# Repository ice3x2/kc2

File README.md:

# kc2

- **[최신 PCB · 주문한 거버 · 인쇄 모델 — hardware](hardware/README.md)**
- [PCB 프로젝트](hardware/PCB/) · [주문한 거버 ZIP](hardware/GERBER/) · [하우징·링 모델](hardware/MODELS/)
- [MX · Choc V1 · Deep Sea 내부 충전형 인쇄 안내](hardware/MODELS/PRINT-filled-plates.md) · [검증 기록](docs/reports/solid-filled-plates-20260913/README.md)
- [자석 홈 옵션 / 무자석 옵션 선택 안내](hardware/MODELS/PRINT_magnetic.md)
- [주문 당시 안내 원본](order.md) — 봉인 해시 보존용입니다. 현재 위치는 위 `hardware` 안내를 보세요.
- [요구사항 원본(SRS)](docs/spec/00.index.md)

새로 clone한 뒤 기존 생성·검증 도구를 사용할 때는 한 번 실행하세요(Python 3.12 이상).

```powershell
python -B -m tools.kc2_current_layout --apply
```

현재 파일은 `hardware/PCB`, `hardware/GERBER`, `hardware/MODELS`에 실제로 저장됩니다. 기존 `hardware/case`와 일부 `hardware/kicad` 경로는 동일 원본을 가리키는 로컬 호환 연결이며 복사본이 아닙니다.

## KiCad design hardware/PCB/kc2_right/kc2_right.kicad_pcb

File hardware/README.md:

# PCB · 주문한 거버 · 하우징 인쇄 파일

요구사항: `CON-ARCH-006`, `CON-ARCH-007`, `OPS-ARCH-006/007`.

하우징을 인쇄하기 전에 [현재 인쇄·조립 안내](MODELS/PRINT-upper-finish.md)의 검증 명령을 실행하세요. 상판의 비기능 내부 틈을 메우고 국부 하향 돌출을 제거하여 아홉 상판 STL의 최저면을 `Z=4.40`으로 공면화한 개정입니다. 검증이 실패하거나 manifest가 없으면 게시가 미완료된 것이므로 인쇄를 보류합니다. 실제 끼움·강도·키캡 간섭·나사 토크는 출력·조립 후 확인해야 합니다.

- `PCB/`: 기존 주문 설계. [왼쪽 PCB](PCB/kc2_left/kc2_left.kicad_pcb), [오른쪽 PCB](PCB/kc2_right/kc2_right.kicad_pcb). 각 KiCad 프로젝트 폴더 전체와 저장소 `third_party` 라이브러리를 유지하세요.
- `GERBER/`: 변경하지 않은 주문 r4 PCB-only 패키지. [왼쪽 제조 ZIP](GERBER/kc2_left-pcb-fabrication-only.zip), [오른쪽 제조 ZIP](GERBER/kc2_right-pcb-fabrication-only.zip), [주문 manifest](GERBER/manifest.json). 이번 기구 개정으로 재주문할 필요는 없습니다.
- `MODELS/`: MX / Choc V1 / Deep Sea Mini 상판과 무자석 / magnetic 하판. 각 종류의 왼쪽 한 개와 오른쪽 A/B 두 STL을 사용합니다. 오른쪽 STEP/F3D는 두 부품을 포함하는 편집·확인용입니다.
- `MODELS/adapters/`: 이번에 변경하지 않은 [기존 링 어댑터](MODELS/adapters/README.md).

PCB는 이전처럼 하판 받침 위에 놓습니다. 외벽은 PCB 윗면보다 1.50 mm 높고 상판 아래쪽을 1.20 mm 감쌉니다. 중앙 좌우 맞댐은 비접촉이며 잠금 요철은 없습니다. 오른쪽 A/B 결합부는 별도 구조입니다. 이전 상판·하판과 새 파일을 섞지 말고 현재 안내의 정확한 15개 STL 링크 중 필요한 종류를 선택하세요.

실리콘 발 배치·접착 검토는 사용자 요청으로 보류했습니다. 예전 발 배치 그림은 이번 하우징의 검증 증거가 아닙니다. 기존 `PRINT-filled-plates.md` 등 과거 안내는 현재 게시 검증을 대체하지 않습니다. 현재 인쇄 안내가 이전 지침보다 우선합니다.

이 기구 개정은 이미 주문한 PCB/Gerber 16개 파일을 변경하지 않으며 새로운 제작·구매·결제 승인을 의미하지 않습니다.

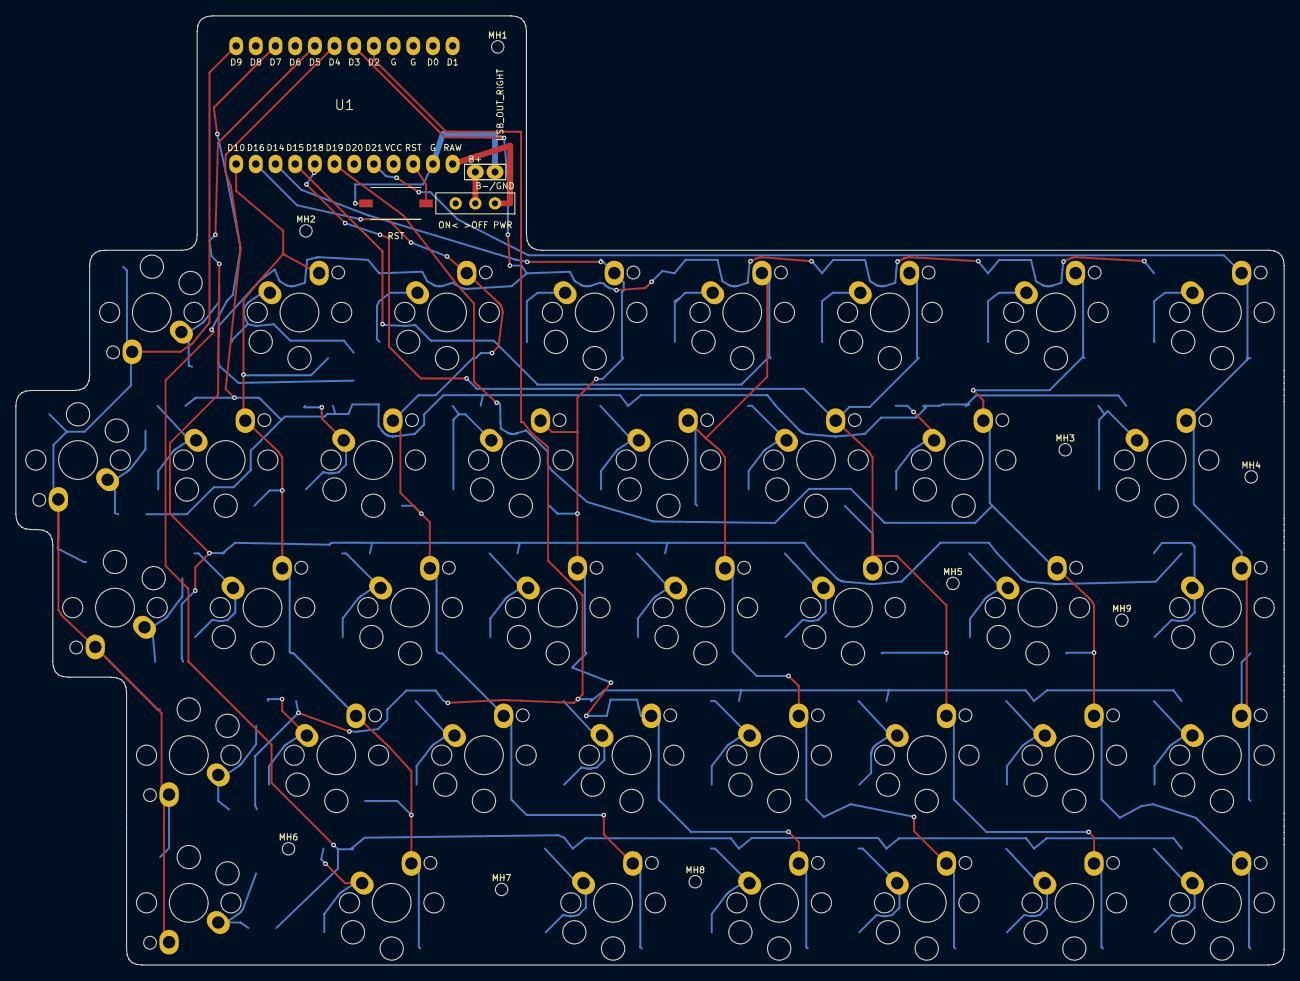
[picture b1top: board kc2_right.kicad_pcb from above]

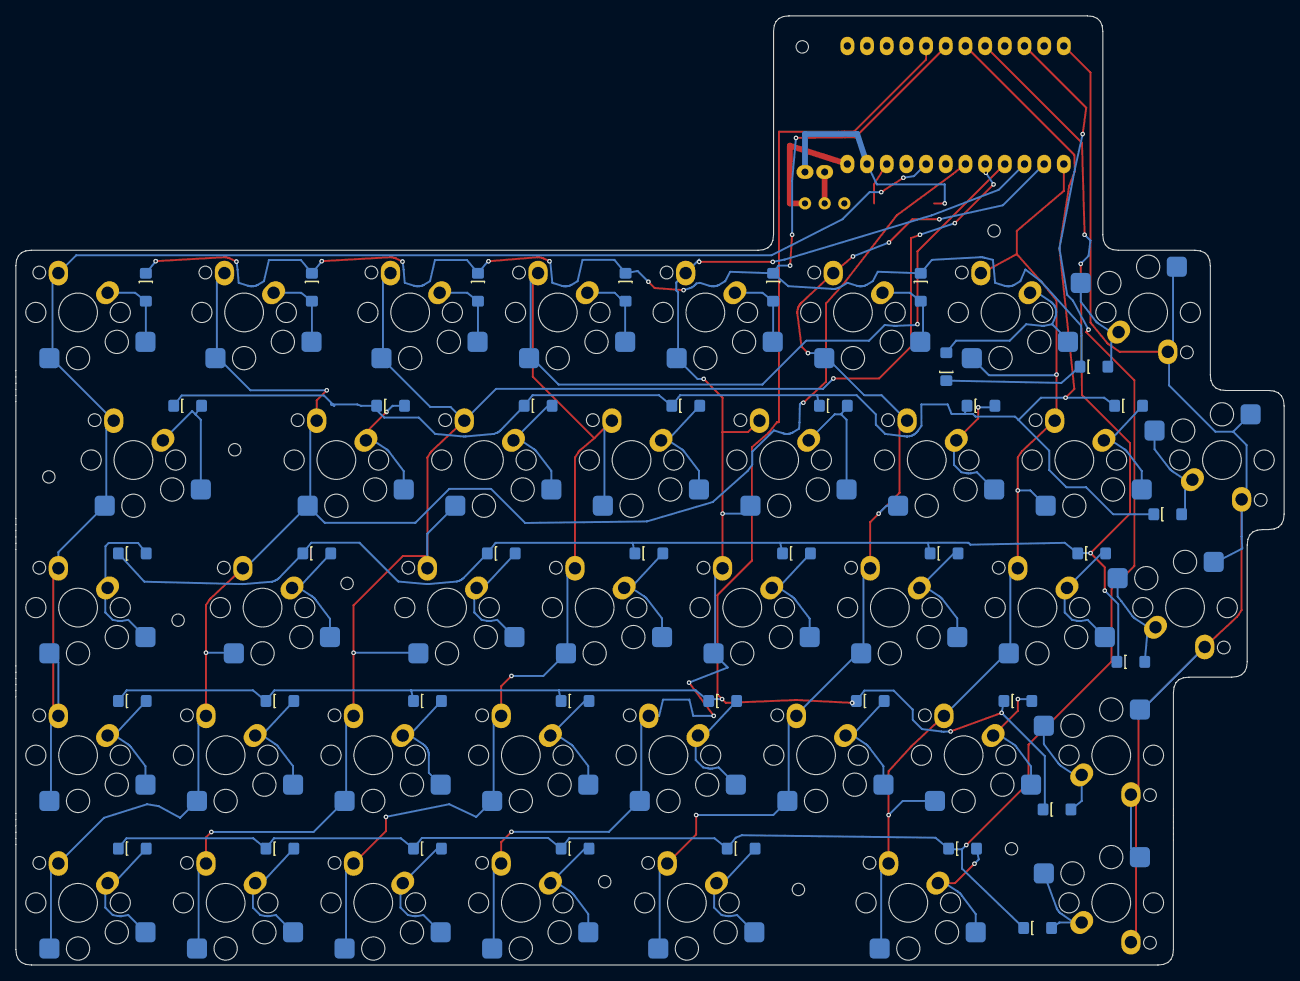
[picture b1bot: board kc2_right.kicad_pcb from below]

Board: 2 copper layers, 163.7 x 122.5 mm, 93 parts (39 on the bottom side), 56 nets.

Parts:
BAT1: 301230_3.7V_100mAh; BAT_301230_30x12mm
BAT_LEAD_SLOT1: BAT_LEAD_NPTH_SLOT_3.6x2.2
D1, D2, D3, D4, D5, D6, D7, D8, D9, D10, D11, D12, D13, D14, D15, D16, D17, D18, D19, D20, D21, D22, D23, D24, D25, D26, D27, D28, D29, D30, D31, D32, D33, D34, D35, D36, D37, D38, D39: 1N4148W-13-F_DiodesInc_SOD123; D_1N4148W_SOD123_HandSolder_DiodesInc
J_BAT1: 301230_DIRECT_SOLDER; BAT_2Pin_PTH_DirectSolder
MH1, MH2, MH3, MH4, MH5, MH6, MH7, MH8, MH9: M1.4_NPTH_1.60; MH_M1.4_NPTH_1.60
SW1: KEY_01; SW_Choc_V2_Socket_MX_THT
SW2: KEY_02; SW_Choc_V2_Socket_MX_THT
SW3: KEY_03; SW_Choc_V2_Socket_MX_THT
SW4: KEY_04; SW_Choc_V2_Socket_MX_THT
SW5: KEY_05; SW_Choc_V2_Socket_MX_THT
SW6: KEY_06; SW_Choc_V2_Socket_MX_THT
SW7: KEY_07; SW_Choc_V2_Socket_MX_THT
SW8: KEY_08; SW_Choc_V2_Socket_MX_THT
SW9: KEY_09; SW_Choc_V2_Socket_MX_THT
SW10: KEY_10; SW_Choc_V2_Socket_MX_THT
SW11: KEY_11; SW_Choc_V2_Socket_MX_THT
SW12: KEY_12; SW_Choc_V2_Socket_MX_THT
SW13: KEY_13; SW_Choc_V2_Socket_MX_THT
SW14: KEY_14; SW_Choc_V2_Socket_MX_THT
SW15: KEY_15; SW_Choc_V2_Socket_MX_THT
SW16: KEY_16; SW_Choc_V2_Socket_MX_THT
SW17: KEY_17; SW_Choc_V2_Socket_MX_THT
SW18: KEY_18; SW_Choc_V2_Socket_MX_THT
SW19: KEY_19; SW_Choc_V2_Socket_MX_THT
SW20: KEY_20; SW_Choc_V2_Socket_MX_THT
SW21: KEY_21; SW_Choc_V2_Socket_MX_THT
SW22: KEY_22; SW_Choc_V2_Socket_MX_THT
SW23: KEY_23; SW_Choc_V2_Socket_MX_THT
SW24: KEY_24; SW_Choc_V2_Socket_MX_THT
SW25: KEY_25; SW_Choc_V2_Socket_MX_THT
SW26: KEY_26; SW_Choc_V2_Socket_MX_THT
SW27: KEY_27; SW_Choc_V2_Socket_MX_THT
SW28: KEY_28; SW_Choc_V2_Socket_MX_THT
SW29: KEY_29; SW_Choc_V2_Socket_MX_THT
SW30: KEY_30; SW_Choc_V2_Socket_MX_THT
SW31: KEY_31; SW_Choc_V2_Socket_MX_THT
SW32: KEY_32; SW_Choc_V2_Socket_MX_THT
SW33: KEY_33; SW_Choc_V2_Socket_MX_THT
SW34: KEY_34; SW_Choc_V2_Socket_MX_THT
SW35: KEY_35; SW_Choc_V2_Socket_MX_THT
SW36: KEY_36; SW_Choc_V2_Socket_MX_THT
SW37: KEY_37; SW_Choc_V2_Socket_MX_THT
SW38: KEY_38; SW_Choc_V2_Socket_MX_THT
SW39: KEY_39; SW_Choc_V2_Socket_MX_THT
SW_PWR1: IMMS-12V_BSI-10; SW_IMMS_12V_BSI10_THT
SW_RST1: NW3-A06-B3 RST; SW_NW3_A06_B3_SMD
U1: nice!nano_v2_socket_24pin; NiceNanoV2_Socket_24Pin_USB_OUT_RIGHT

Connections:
BAT+: J_BAT1.1, SW_PWR1.1
GND: J_BAT1.2, SW_RST1.2, U1.GND_C
NN_B+: SW_PWR1.2, U1.RAW
RK01_D: D1.2, SW1.2
RK02_D: D2.2, SW2.2
RK03_D: D3.2, SW3.2
RK04_D: D4.2, SW4.2
RK05_D: D5.2, SW5.2
RK06_D: D6.2, SW6.2
RK07_D: D7.2, SW7.2
RK08_D: D8.2, SW8.2
RK09_D: D9.2, SW9.2
RK10_D: D10.2, SW10.2
RK11_D: D11.2, SW11.2
RK12_D: D12.2, SW12.2
RK13_D: D13.2, SW13.2
RK14_D: D14.2, SW14.2
RK15_D: D15.2, SW15.2
RK16_D: D16.2, SW16.2
RK17_D: D17.2, SW17.2
RK18_D: D18.2, SW18.2
RK19_D: D19.2, SW19.2
RK20_D: D20.2, SW20.2
RK21_D: D21.2, SW21.2
RK22_D: D22.2, SW22.2
RK23_D: D23.2, SW23.2
RK24_D: D24.2, SW24.2
RK25_D: D25.2, SW25.2
RK26_D: D26.2, SW26.2
RK27_D: D27.2, SW27.2
RK28_D: D28.2, SW28.2
RK29_D: D29.2, SW29.2
RK30_D: D30.2, SW30.2
RK31_D: D31.2, SW31.2
RK32_D: D32.2, SW32.2
RK33_D: D33.2, SW33.2
RK34_D: D34.2, SW34.2
RK35_D: D35.2, SW35.2
RK36_D: D36.2, SW36.2
RK37_D: D37.2, SW37.2
RK38_D: D38.2, SW38.2
RK39_D: D39.2, SW39.2
RST: SW_RST1.1, U1.RST
R_COL0: SW1.1, SW9.1, SW17.1, SW25.1, SW33.1, U1.D9
R_COL1: SW2.1, SW10.1, SW18.1, SW26.1, SW34.1, U1.D10
R_COL2: SW3.1, SW11.1, SW19.1, SW27.1, SW35.1, U1.D16
R_COL3: SW4.1, SW12.1, SW20.1, SW28.1, SW36.1, U1.D14
R_COL4: SW5.1, SW13.1, SW21.1, SW29.1, SW37.1, U1.D15
R_COL5: SW6.1, SW14.1, SW22.1, SW30.1, SW38.1, U1.D18
R_COL6: SW7.1, SW15.1, SW23.1, SW31.1, SW39.1, U1.D19
R_COL7: SW8.1, SW16.1, SW24.1, SW32.1, U1.D21
R_ROW0: D1.1, D2.1, D3.1, D4.1, D5.1, D6.1, D7.1, D8.1, U1.D3
R_ROW1: D9.1, D10.1, D11.1, D12.1, D13.1, D14.1, D15.1, D16.1, U1.D4
R_ROW2: D17.1, D18.1, D19.1, D20.1, D21.1, D22.1, D23.1, D24.1, U1.D5
R_ROW3: D25.1, D26.1, D27.1, D28.1, D29.1, D30.1, D31.1, D32.1, U1.D2
R_ROW4: D33.1, D34.1, D35.1, D36.1, D37.1, D38.1, D39.1, U1.D7

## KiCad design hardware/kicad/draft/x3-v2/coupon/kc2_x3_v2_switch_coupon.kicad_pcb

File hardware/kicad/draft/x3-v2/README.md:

# KC2 X3 V2 routed draft

Requirements: `CON-ARCH-004`, `CON-ARCH-006`, `CON-ARCH-007`, `REL-ARCH-001`

Status: **DIGITAL PASS - ORDER READY: NO**. Exact V2 service geometry and nets
and fresh KiCad 10.0.3 DRC pass digitally. Ordering remains blocked by exact
301230 pack/protection/lead and `J_BAT1` drill selection, controller-stack fit,
solder/strain-relief/service tests, IMMS power-transition and BLE tests,
populated coupon/first articles, and housing/fastener/2.0 N deflection tests.

These V2 files live only under `hardware/kicad/draft/x3-v2/`. The promoted
`hardware/kicad/kc2_left/` and `hardware/kicad/kc2_right/` projects are the
older verified X3 variant and are not V2 implementation evidence.

## Assembly modes

The two switch modes are mutually exclusive at every key position:

- Choc V2 / PG1353-class: install a Kailh `CPG135001S30`-class hot-swap socket
  on the PCB bottom. Do not directly solder the switch.
- Cherry MX-style 5-pin PCB-mount: install the switch from the PCB top and
  directly solder its two electrical pins. No MX hot-swap socket is supported.
- Choc V1 / PG1350, Choc V2 direct-solder, and MX hot-swap are unsupported.
- Never install both a Choc socket and an MX switch at one key position.

The intended switch remains the Kailh Deep Sea low-profile / PG1353 family,
but its exact manufacturer MPN and controlled drawing revision are still
pending. `Deep Sea`, `Deep Sea Whale`, a reseller nickname, or a family name
is not an orderable part identity. Do not order the switch until those two
fields are bound to the purchased part and its controlled drawing.

The owned hybrid footprint includes an explicit bottom courtyard from
`(-10.25,1.20)` to `(5.25,8.50)` mm. It encloses the complete bottom socket
body and both B.Cu lands with a `0.25 mm` manufacturing allowance.

The left and right boards use their physical split-keyboard orientations. The
bottom-side socket pattern must be read from the PCB bottom; the 1:1 bottom PDF
is already mirrored for a physical bottom view.

## Matrix diode and polarity

The active V2 BOM contains exactly 70 Diodes Incorporated `1N4148W-13-F`
matrix diodes in flat SOD-123 packages, controlled by `DS30086 Rev. 31-2`.
All are assembled on `B.Cu`. Pin/pad 1 is the cathode connected to the row net; pin/pad
2 is the anode connected to the per-key switch net. A physical bottom view is
mirrored relative to KiCad's top/front view, so place the cathode band toward
the marked pad 1 rather than relying on an assumed left/right direction.

The firmware contract remains `col2row`, active-high columns, and active-high
row inputs with pull-downs. The existing pinned build remains zero-wait: no
extra delay before reading inputs and no delay between driven columns. Do not
change those scan delays until a populated physical coupon has passed both
3.0 V and 3.3 V maximum same-row and maximum same-column stress tests. Those
tests remain pending, so these digitally verified boards are not orderable.

## Joined spacing

The joined reference places the right half `0.80 mm` farther outward than the
ordinary `19.05 mm` one-unit transform. Corresponding Choc V2 and MX assembly
modes are evaluated with the same selected cap envelope for each physical key.
All five actual seam pairs have a nominal `1.80 mm` cap-to-cap gap and a
`3.80 mm` row-center PCB gap:

| Row | Pair | Cap widths (left/right) | Center pitch | Center-to-PCB-edge (left/right) |
|---:|---|---:|---:|---:|
| 0 | `6`-`7` | `18.05 / 18.05 mm` | `19.85 mm` | `8.025 / 8.025 mm` |
| 1 | `T`-`Y` | `18.05 / 18.05 mm` | `19.85 mm` | `8.025 / 8.025 mm` |
| 2 | `G`-`H` | `18.05 / 18.05 mm` | `19.85 mm` | `8.025 / 8.025 mm` |
| 3 | `B`-`N` | `18.05 / 18.05 mm` | `19.85 mm` | `8.025 / 8.025 mm` |
| 4 | `Space`-`B` | `32.3375 / 18.05 mm` | `26.99375 mm` nominal (`26.9937 mm` in the routed coordinate serialization) | `15.16875 / 8.025 mm` nominal |

The two complete closed Edge.Cuts outlines are compared segment by segment,
including horizontal stair transitions. Their exact minimum is `1.10 mm`,
created by a direction-aware `0.55 mm` transition stagger. PCBWay's published
`+/-0.20 mm` CNC outline tolerance gives a conservative two-edge lower bound
of `0.70 mm` at that limiting transition. This is digital nominal geometry;
actual half-to-half housing registration and assembled cap/switch play still
require a printed first article.

After soldering an MX switch, trim both electrical terminals after inspection.
The 2.50 mm lower plate has exterior-bottom-open cutouts through the full plate
height for every MX terminal and solder joint, rather than a closed component
cavity. The lateral solder-fillet model includes a 0.30 mm allowance.

The Choc socket and 1N4148W SOD-123 solder-fillet models each include a 0.30 mm
lateral allowance. The routed boards pass the current digital diode gates:
the minima across both halves are 1.946 mm to unused switch NPTH, 1.125 mm to
switch pads and unrelated exposed copper, 2.225 mm to socket bodies, 0.525 mm
between diode and switch-assembly fillet envelopes, and 1.975 mm from the
diode fillet envelope to Edge.Cuts. The diode-to-unrelated-route minima are
0.737 mm left and 0.545 mm right, both above the 0.10 mm gate. Every diode
pad has an unobstructed cardinal solder-tool approach. The enlarged KC2 hand-
solder land is deliberately not the manufacturer's recommended land: implemented
pads are 1.40 x 1.55 mm at 3.60 mm centers, while the official suggested pads
are 0.90 x 0.95 mm at 4.05 mm centers. Regenerated housing evidence provides
0.35 mm cutout XY clearance, 1.525 mm minimum diode perimeter land, and 1.85 mm
nominal / 1.55 mm post-tolerance diode-to-desk clearance. The Choc socket is the
overall open-component limiter at 1.10 mm nominal / 0.80 mm post-tolerance.
This remains digital
evidence only; physical retention, deflection, and populated-coupon tests are
still required before ordering.

## M1.4 retention prototype

The PCB contains eight left and nine right `MH*` features using the owned
`MH_M1.4_NPTH_1.60` footprint. Each is an unnetted, copper-free `1.60 mm`
round NPTH. Each hole is visibly numbered `MH1..MH8` on the left and
`MH1..MH9` on the right using `0.80 mm` / `0.15 mm` front-silkscreen text.
Service is modeled with keycaps removed and either supported switch
type still installed. A final `3.00 mm` vertical PH0 driver envelope and a
provisional non-countersunk rounded pan/button head envelope of maximum
`3.00 x 1.20 mm` clear the modeled Choc V2 and MX assemblies with a separate
`0.25 mm` XY reserve. The driver envelope already includes its search reserve
and must not be buffered a second time.

The matching lower housing provides a `3.00 mm` zero-gap support land and desk
column at every hole, with a provisional `1.10 x 2.80 mm` blind pilot and a
`0.70 mm` closed bottom at the common Z=-1.00 mm desk datum. A separate exact
one-to-one network of 31-left/39-right `2.40 mm` key-load feet provides every
switch center with a local desk load path whose worst center-to-support-edge
distance is `4.3902 mm`, within the `4.40 mm` SOD-123/P3 bound; mounting columns are not credited as typing-load
supports. The provisional 4.00 mm under-head screw
length, exact screw and driver, full-pattern registration, installation and
stripping torque, ten service cycles, keycap-skirt clearance, and 2.0 N
deflection must be proven on physical coupons. These digital files are not a
fastener purchase recommendation and remain not orderable.

## Battery service path

Each half uses one nominal `30.00 x 12.00 x 3.00 mm`, 3.7 V, 100 mAh
301230-class pack above the carrier PCB and below the socketed nice!nano. The
battery centers are left `(131.7125, 50.7500)` and right
`(78.4000, 50.7500)` mm, with the 30 mm axis parallel to the U1 socket rows.
The exact manufacturer/MPN, single-cell protection status, maximum swollen
thickness, lead-exit drawing, and pull limit remain procurement gates.

Only the pack's pre-attached insulated leads are soldered to `J_BAT1`; do not
solder a bare pouch tab and do not add an A2501, JST, or other detachable
battery connector. `J_BAT1` is left `(115.8125, 59.4000)` R180 and right
`(94.3000, 59.4000)` R0. Its visible assembly marks identify pad 1 `B+` and
pad 2 `B-/GND`; the electrical pad nets remain `BAT+` and `GND`, respectively.
The [official nice!nano documentation](https://nicekeyboards.com/docs/nice-nano/)
identifies the carrier's `RAW` and `GND` pins as the battery-positive and
battery-negative connections, so no extra net tie is required.
`BAT_LEAD_SLOT1` remains an unnetted, copper-free
strain-relief feature identified by the exact board text
`BAT STRAIN RELIEF`, at left `(117.9125, 50.7500)` and right
`(92.2000, 50.7500)` mm; it is not a lower battery exit.

The electrical path is
`J_BAT1 BAT+ -> SW_PWR1 pad 1 common -> pad 2 ON -> NN_B+ -> U1 RAW`. Pad 3 is
NC. J_BAT1 B-/GND remains directly connected to
local GND and U1 GND. Keep BAT+ and its GND return paired in the USB-side
corridor and outside the antenna keepout. The lower housing has no TW301525 or
301230 battery-body cavity; it provides only the required U1, J_BAT1,
strain-relief, IMMS lead, and solder-fillet openings.

## Compact controller tab

The V2-only compact-controller layout keeps all 70 key centers and all 17
numbered mounting-hole centers fixed. U1 centers are left
`(132.7125, 50.7500)` and right `(77.4000, 50.7500)` mm. The top Edge.Cuts
centerline is `Y=39.2500 mm`, and the nominal board height is `122.50 mm`.

POWER and RESET occupy the controller-key gap. `SW_PWR1` is left
`(115.8125, 63.4500)` R0 and right `(94.3000, 63.4500)` R180. `SW_RST1` is
left `(126.0625, 63.4500)` R0 and right `(84.0500, 63.4500)` R180, with pad
1=RST on the POWER/USB-facing side and pad 2=GND on the keyboard-center side.
Top-view absolute order is left `PWR|RST` and right `RST|PWR`; from each
USB-facing outer edge toward the antenna, the service order is POWER then
RESET. The centers are 10.25 mm apart, giving 2.20 mm nominal controlled-body
clearance, 3.20 mm reset-body clearance to the nearest keycap envelope, and
at least 2.03 mm reset-courtyard clearance to U1 socket copper.

Each placed `SW_PWR1` retains the owned STEP model. That STEP is a nominal
collision proxy only: the exact purchased manufacturer/MPN and controlled
drawing are pending, and `IMMS-12V` / `BSI-10` equivalence is not assumed.

This V2 contract supersedes the historical X3 no-carrier-power,
USB-under-reset, and antenna-side-reset instructions only for `kc2-x3-v2`.
The exact pack stack, USB shell/cable, POWER/RESET access, controller removal,
lead strain relief, keycap clearance, and actuation support still require
physical first-article evidence. The digital package remains not orderable.

## Outputs

- Routed boards: `kc2_left-x3-v2/` and `kc2_right-x3-v2/`
- Physical fit coupon CAD: `coupon/`
- Draft Gerber/Excellon packages: `fabrication/`
- JLCPCB upload-preview archives: `fabrication/kc2_x3_v2_left_jlcpcb.zip`,
  `fabrication/kc2_x3_v2_right_jlcpcb.zip`, and
  `fabrication/kc2_x3_v2_coupon_jlcpcb.zip`
- 1:1 top/bottom assembly PDFs: `mechanical/`
- KiCad 3D inspection renders: `renders/`
- Housing clearance evidence: `../../../case/draft/x3-v2/`

The fabrication, mechanical, and housing derivatives were regenerated from
the current left/right board hashes
`7de01a7f0c60585c1845ab3ad17c2b7d18e17ae8c2090a3594e6edf0cbf9d7cf` and
`b4173e7bb16189690b06bc3a8d6487e8c56e7e69100e6c04d798d687213f2adc`.
Their dedicated V2 verifiers pass. The joined SVG/PNG set was regenerated from
the same current boards and reports 1.1000 mm minimum Edge.Cuts clearance and
1.8000 mm cross-seam keycap gap. All outputs remain digital draft evidence and
do not change **ORDER READY: NO**.

The JLCPCB upload-preview archives contain exactly 15 root-level manufacturing
files each: copper, mask, paste, silkscreen, Edge.Cuts, plated/non-plated drill,
drill maps/report, and the Gerber job. They intentionally exclude the BOM JSON
and CSV carried by the broader traceability archives. The machine-readable
profile in `fabrication/kc2_x3_v2_fabrication_manifest.json` records 2-layer
FR-4, 1.6 mm, 1 oz, ENIG, green solder mask, white silkscreen, hand assembly,
and both-side tented vias with a 0.50 mm maximum tented drill. The verifier
checks the source-board tenting settings and confirms that neither mask Gerber
opens at any via center. JLCPCB production-file confirmation must be enabled
and the engineer-generated production Gerbers must be downloaded and reviewed
before approval. These are prototype upload previews only while the physical
coupon, housing/fastener, controller-service, and power/RF evidence remains
pending.

The coupon contains conservative representative 0-degree and 180-degree
bottom socket orientations plus a 5-pin MX direct-solder sample at 19.05 mm
pitch. The 180-degree sample deliberately exercises the rotated/mirrored
assembly risk required by `CON-ARCH-004` AC-9. Its CAD and fabrication package
do not satisfy the physical evidence gate by themselves. A populated coupon
must additionally verify 1N4148W polarity and solder access plus the pending 3.0 V
and 3.3 V zero-wait same-row/same-column matrix stress cases.

## Reproduction and verification

Run PCB tools with KiCad 10 Python:

Run these commands from the repository root. The housing verifier additionally
requires the documented CadQuery environment. The exact executable release
gates for the active V2 target are `tools.verify_kc2_x3_v2` and the dedicated
V2 fabrication, mechanical, outline, coupon, firmware, and housing verifiers
below. Apply the `kc2-pcb-preflight` component-by-component and
circuit-by-circuit review workflow as an additional audit. Its bundled CLI
supports the historical `--variant x3` path only; an `ORDER READY` result from
that historical X3 run is not evidence for `kc2-x3-v2`.

`tools.verify_kc2_x3_v2` exits `0` only when every digital and physical gate
passes, `1` on a digital error, and `2` when digital checks pass but required
physical evidence is still pending. The current expected result is exit `2`.

```powershell
$kpy = 'C:\Program Files\KiCad\10.0\bin\python.exe'
& $kpy -m tools.generate_kc2_pcbs --variant x3-v2 --output-dir tmp_x3_v2_clean
& $kpy -m tools.render_kc2_x3_joined --variant x3-v2 --placement-mode key-pitch --scale 5 --output-dir hardware/kicad/draft/x3-v2/renders
& $kpy -m tools.verify_kc2_x3_v2
& $kpy -m tools.verify_kc2_x3_v2_coupon
& $kpy -m tools.verify_kc2_x3_v2_outline
& $kpy -m tools.verify_kc2_x3_v2_fabrication
& $kpy -m tools.verify_kc2_x3_v2_mechanical
& $kpy -m tools.verify_kc2_x3_v2_zmk_firmware
python -m tools.verify_kc2_x3_v2_housing
```

The render command writes both SVG and PNG evidence. If Pillow is unavailable
in KiCad Python, it automatically uses an installed Chromium-family browser;
on Windows it detects Microsoft Edge in its standard install locations. Set
`KC2_HEADLESS_BROWSER` to an explicit browser executable when auto-detection is
not appropriate. The focused test launches this exact CLI with the active
KiCad Python and verifies that both fresh PNG files have valid dimensions.

The isolated generator output is intentionally unrouted. The committed board
files include the reviewed route completion and must retain KiCad DRC results
of zero violations and zero unconnected items. After producing both fresh DRC
JSON reports, regenerate the exact board/report evidence binding before running
the release verifier:

```powershell
& "C:\Program Files\KiCad\10.0\bin\python.exe" -B -m tools.generate_kc2_x3_v2_drc_evidence
& "C:\Program Files\KiCad\10.0\bin\python.exe" -B -m tools.verify_kc2_x3_v2
```

`kc2_x3_v2_drc_evidence.json` binds each current board and `.kicad_pro`
SHA-256 to its DRC report SHA-256, schema, source filename, KiCad version,
report date, included severity classes, and the project's `Default` netclass
clearance. The release verifier requires that clearance to remain at least
`0.30 mm`, a KiCad 10.x report, a valid ISO timestamp, and both `error` and
`warning` coverage; `exclusion` is the only optional additional severity. A
changed board, project, or report cannot pass against stale evidence.

When only the generated outline policy changes, use
`tools.repair_kc2_x3_v2_compact_edge --sync-edge-cuts-from <fresh-board>`.
The command rejects non-rigid switch geometry, replaces only Edge.Cuts, and is
covered by route/footprint-preservation and idempotence tests.

The current compact-controller, mounting-hole-aware trackless inputs are
`autoroute/kc2_left-x3-v2-70-1n4148w-p3.dsn` and
`autoroute/kc2_right-x3-v2-70-1n4148w-p3.dsn`; they contain exactly
eight and nine visibly numbered M1.4 NPTHs. Their reviewed controller-r3 SES files bind the
moved controller/reset fanout and shortened outline. Against empty-track
generated boards, the finalizer imports those sessions and applies only the
exact, precondition-checked edge cleanup:

```powershell
& "C:\Program Files\KiCad\10.0\bin\python.exe" -B -m tools.finalize_kc2_x3_v2_routes `
  hardware/kicad/draft/x3-v2/kc2_left-x3-v2/kc2_left-x3-v2.kicad_pcb `
  --import-controller-compact-session hardware/kicad/draft/x3-v2/autoroute/kc2_left-x3-v2-70-1n4148w-p3.ses
& "C:\Program Files\KiCad\10.0\bin\python.exe" -B -m tools.finalize_kc2_x3_v2_routes `
  hardware/kicad/draft/x3-v2/kc2_right-x3-v2/kc2_right-x3-v2.kicad_pcb `
  --import-controller-compact-session hardware/kicad/draft/x3-v2/autoroute/kc2_right-x3-v2-70-1n4148w-p3.ses
```

The helper rejects wrong controller/reset/switch geometry, stale sessions, and
partial or unexpected nonempty routes. Both importers verify complete matrix connectivity,
reproduce the committed route exactly, and are covered by second-run
idempotence tests. The retained deterministic route reconstruction has final track/via counts of
590 left and 766 right, with route digests
`b8adeac705f846714f7f201b63487369ef486cb1624df8d0ddbb8cde3053e316`
and `530d6927eacd7e57a48cb6c62e5c5916ef1f4b3f21d67b592e80962ef7af4c1b`.
Running either command against its already exact committed board is a verified
no-op. The generation manifest binds each current controller-r3 DSN and
reviewed controller-r3 SES by SHA-256. It also verifies both
current DSN global/default clearance rules remain at least `300` internal units
(`0.30 mm` at the recorded DSN resolution).

The project explicitly ignores five KiCad diagnostic classes: missing
courtyard, track-not-centered-on-via, tuning-profile track geometry,
symbol/footprint-filter mismatch, and footprint component-type mismatch.
These are generated-board metadata, custom hybrid-footprint library, or
non-applicable tuning diagnostics. The
electrical implications remain covered by exact footprint geometry checks,
matrix-island connectivity checks, NPTH copper-free checks, Gerber/Excellon
inspection, and zero DRC violations/unconnected items.

The production release gate compares every placed 1N4148W pad, B.Fab body,
courtyard, and mirrored B.Silkscreen cathode mark against the KC2-owned
footprint. It also compares every hybrid-switch pad/NPTH and the side-specific
24-pad nice!nano socket against its owned footprint, requires the matching
front-silkscreen `USB_OUT_LEFT`/`USB_OUT_RIGHT` label, and hard-checks
`SW_RST1` pad 1=`RST`, pad 2=`GND`.

Official geometry references:

- Kailh Choc V2 switch: https://www.kailhswitch.com/mechanical-keyboard-switches/key-switches/kailh-low-profile-switch-choc-v2.html
- Kailh socket drawing: https://www.kailhswitch.com/uploads/15927/files/CPG135001S30.pdf?rnd=925
- Cherry MX2A 5-pin datasheet: https://www.cherry.de/fileadmin/media/Industrial/Switch/MX_BLACK/Data_sheet_MX2A_Black.pdf
- Diodes Incorporated 1N4148W product page: https://www.diodes.com/part/view/1N4148W/
- Diodes Incorporated DS30086 Rev. 31-2 datasheet: https://www.diodes.com/datasheet/download/1N4148W.pdf
- nice!nano v2 pinout and schematic: https://nicekeyboards.com/docs/nice-nano/pinout-schematic/

## Component and terminal audit

The 2026-08-31 procurement audit compares the placed footprints with the
published part drawings rather than relying only on KiCad DRC. `PASS` below
means the nominal PCB land pattern matches the cited drawing; it does not
replace incoming inspection or the physical evidence gates.

| Placed item | Published body / terminal contract | Actual KC2 footprint | Result |
|---|---|---|---|
| nice!nano v2 `U1` | Published plan `34.1 x 18.3 mm`; official total thickness `3.2 mm` and official Pro Micro pinout. B+ and B- are not socketed; `RAW` and `GND` are their respective carrier equivalents. | Conservative collision envelope `34.1 x 18.3 mm`; 2 x 12 PTH, `2.54 mm` longitudinal pitch, `15.24 mm` row spacing, pad `1.80 mm`, drill `0.95 mm`; `RAW=NN_B+`, `GND_C=GND`, `RST=RST`. | Plan/pinout PASS; exact female socket and pin-leg MPN/tail height PENDING. |
| Kailh Choc V2 socket | Kailh `CPG135001S30`, drawing `KH-PS-1702-35` Rev D; T=1.6 recommended pattern with `2.60 mm` contacts and specified NPTH locations. | Bottom socket body `9.55 x 6.80 mm`, B.Cu pads `2.60 mm`, exact official mechanical holes; duplicate pads 1 and 2 share the MX electrical nets. | Socket PASS; exact mating Kailh switch MPN/drawing PENDING. |
| Cherry MX alternative | Official MX2A 5-pin PCB-fixation variants; nominal `15 x 15 mm` body and two electrical plus three fixation terminals. | F.Fab `15 x 15 mm`; electrical pads `2.50 mm` with `1.50 mm` drill plus `5.00/3.00/1.65 mm` fixation NPTHs. | Nominal 5-pin geometry PASS; exact optional MX MPN PENDING. |
| `1N4148W-13-F` diode | Diodes Incorporated SOD-123, body max `2.85 x 1.70 x 1.35 mm`, terminal span max `3.85 mm`; suggested pads `0.90 x 0.95 mm` at `4.05 mm` centers; pin 1 cathode, pin 2 anode. | B.Fab `2.85 x 1.70 mm`; controlled hand-solder pads `1.40 x 1.55 mm` at `3.60 mm` centers, classified as a KC2 enlargement rather than the manufacturer land; pad 1 row/cathode, pad 2 per-key/anode. | Digital geometry/polarity PASS; populated solder/scan coupon PENDING. |
| `SW_PWR1` | SM Switch `BSI-10`: `10 x 2.5 x 6.4 mm`, `1.6 mm` travel, three `0.6 mm` pins on `2.54 mm` pitch, recommended `0.8 mm` drills; terminal 1 common. | F.Fab `10 x 2.5 mm`, three `1.60 mm` pads / `0.80 mm` drills at `2.54 mm`; pad 1 `BAT+`, pad 2 `NN_B+`, pad 3 NC. | Geometry/net PASS; exact purchased MPN/drawing and former IMMS equivalence PENDING. |
| `SW_RST1` | DeviceMart `NW3-A06-B3`, nominal body `6.1 x 3.7 mm`. | Controlled body `6.1 x 3.7 mm` inside an `8.0 x 3.7 mm` lead-span drawing; SMD pads `1.75 x 1.00 mm`; pad 1 RST, pad 2 GND. | Nominal PASS; purchased-lot drawing/actuation test PENDING. |
| `BAT1` / `J_BAT1` | Nice Keyboards recommends a rechargeable 3.7 V 301230 cell; exact protected-pack maximum, swelling and lead drawing are supplier-specific. | Nominal body `30 x 12 x 3 mm`; direct-lead pads `2.20 x 1.80 mm`, drill `0.90 mm`, pitch `2.54 mm`; pad 1 BAT+, pad 2 GND/B-. | Nominal only; exact protected pack, lead diameter and maximum envelope BLOCK ORDER. |
| `MH*` | Provisional M1.4 non-countersunk rounded head up to `3.00 x 1.20 mm`. | Copper-free unnetted `1.60 mm` NPTH with housing pilot `1.10 x 2.80 mm`. | Digital clearance PASS; exact screw/driver MPN and physical torque/deflection PENDING. |

Dimension and terminal sources additionally used by this audit:

- nice!nano mounting/battery guidance: https://nicekeyboards.com/docs/nice-nano/
- nice!nano installation and B+/B-/RAW/GND guidance: https://nicekeyboards.com/docs/nice-nano/getting-started/
- nice!nano published reseller dimensions: https://mechboards.co.uk/products/nice-nano-v2
- SM Switch BSI-10 drawing: https://pf02.ickimg.com/datasheet/upload/2023/10/07/BSI-10.pdf
- DeviceMart NW3-A06-B3 dimensions: https://www.devicemart.co.kr/goods/view?no=1322056
- Diodes Incorporated 1N4148W: https://www.diodes.com/part/view/1N4148W/

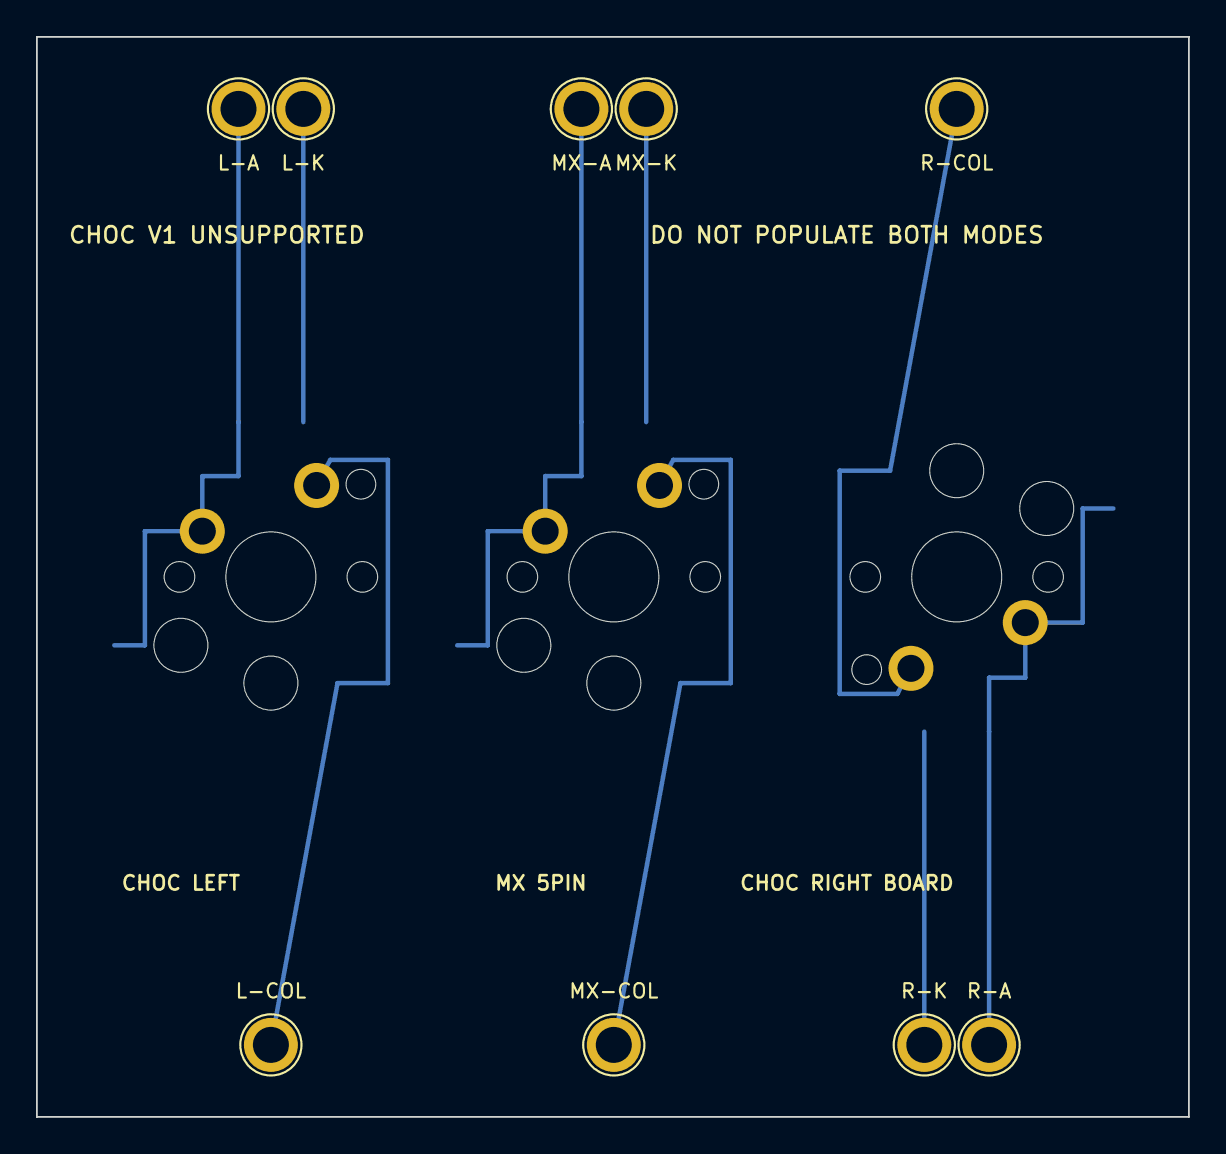
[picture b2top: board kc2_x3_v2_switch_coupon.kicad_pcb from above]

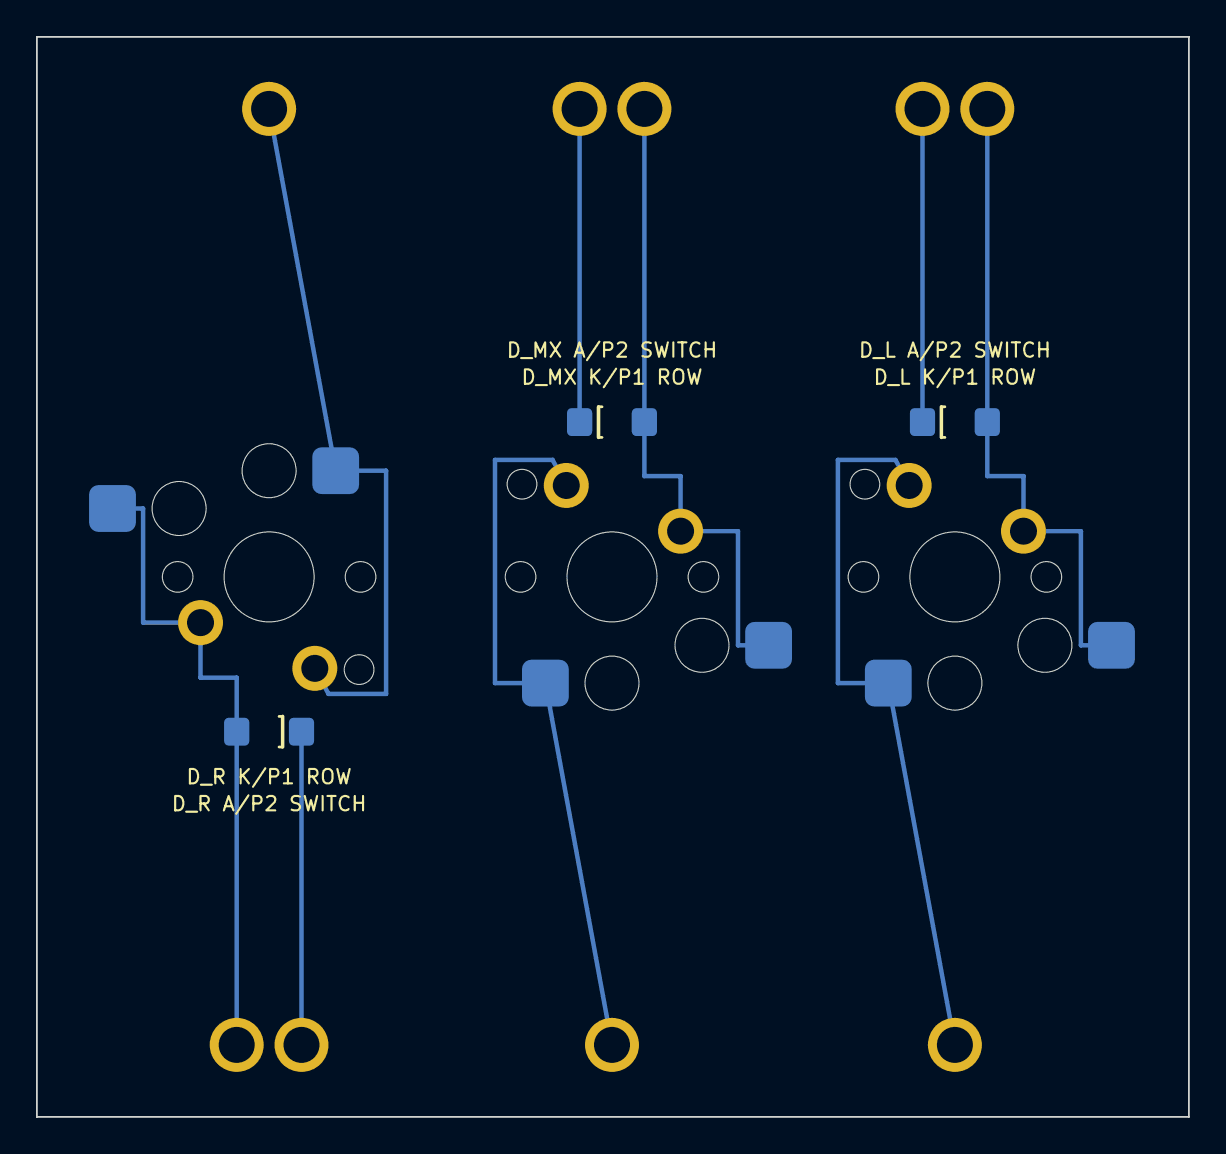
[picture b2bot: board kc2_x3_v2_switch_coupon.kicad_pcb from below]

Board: 2 copper layers, 64.0 x 60.0 mm, 15 parts (3 on the bottom side), 9 nets.

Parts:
D_L: 1N4148W-13-F_DiodesInc_SOD123; D_1N4148W_SOD123_HandSolder_DiodesInc
D_MX: 1N4148W-13-F_DiodesInc_SOD123; D_1N4148W_SOD123_HandSolder_DiodesInc
D_R: 1N4148W-13-F_DiodesInc_SOD123; D_1N4148W_SOD123_HandSolder_DiodesInc
SW_L: CHOC_V2_SOCKET_OR_MX_5PIN_THT; SW_Choc_V2_Socket_MX_THT
SW_MX: CHOC_V2_SOCKET_OR_MX_5PIN_THT; SW_Choc_V2_Socket_MX_THT
SW_R: CHOC_V2_SOCKET_OR_MX_5PIN_THT; SW_Choc_V2_Socket_MX_THT
TP_L_ANODE: 2.0mm_PTH_SERVICE_PROBE; TestPoint_Plated_Hole_D2.0mm
TP_L_COL: 2.0mm_PTH_SERVICE_PROBE; TestPoint_Plated_Hole_D2.0mm
TP_L_ROW: 2.0mm_PTH_SERVICE_PROBE; TestPoint_Plated_Hole_D2.0mm
TP_MX_ANODE: 2.0mm_PTH_SERVICE_PROBE; TestPoint_Plated_Hole_D2.0mm
TP_MX_COL: 2.0mm_PTH_SERVICE_PROBE; TestPoint_Plated_Hole_D2.0mm
TP_MX_ROW: 2.0mm_PTH_SERVICE_PROBE; TestPoint_Plated_Hole_D2.0mm
TP_R_ANODE: 2.0mm_PTH_SERVICE_PROBE; TestPoint_Plated_Hole_D2.0mm
TP_R_COL: 2.0mm_PTH_SERVICE_PROBE; TestPoint_Plated_Hole_D2.0mm
TP_R_ROW: 2.0mm_PTH_SERVICE_PROBE; TestPoint_Plated_Hole_D2.0mm

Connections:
D_L_ANODE: D_L.2, SW_L.2, TP_L_ANODE.1
D_L_COL: SW_L.1, TP_L_COL.1
D_L_ROW: D_L.1, TP_L_ROW.1
D_MX_ANODE: D_MX.2, SW_MX.2, TP_MX_ANODE.1
D_MX_COL: SW_MX.1, TP_MX_COL.1
D_MX_ROW: D_MX.1, TP_MX_ROW.1
D_R_ANODE: D_R.2, SW_R.2, TP_R_ANODE.1
D_R_COL: SW_R.1, TP_R_COL.1
D_R_ROW: D_R.1, TP_R_ROW.1

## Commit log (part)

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2026-06-03 Finalize KC2 routed PCB draft
2026-06-03 Add KC2 hotswap PCB variant
2026-06-03 Add KC2 x1 hand-solder diode variant
2026-06-03 Add KC2 x2 socket and solder variant
2026-06-04 feat: KC2 X3 무보강판 변형과 SpecKiwi SRS 워크플로 도입
    - generate_kc2_pcbs.py x3 변형: x2 전기 스택 + no-stabilizer 77키 layout, KiCad 8/9/10 share 자동 탐색, 임베디드 footprint fallback
    - verify_kc2_connectivity.py: 레이어 인식 넷/diode/row-col/컨트롤러 핀 매핑 검증 (좌우 X3 PASS)
    - kc2_left/right-x3 보드, autoroute dsn/ses, x3 manifest 생성
    - docs/spec.md·research 문서에 X3 결과 반영, kc2_right-x2.kicad_pro KiCad 재저장 동기화
    - SpecKiwi SRS 도입: CLAUDE.md/AGENTS.md 작업 규약, docs/rule 작성 규칙, docs/spec/ 스캐폴딩과 20.no-stabilizer-layout SSOT
2026-06-04 fix: KC2 X3 발주 차단 해소
    - nice!nano 좌/우 전용 풋프린트 추가 및 controller/switch/power 추적성 정리
    - switch pad island routing, edge clearance, DRC error/warning 해소
    - 좌/우 PCB, DSN/SES, Gerber/Excellon/fabrication zip/render/DRC JSON 갱신
2026-06-05 fix: KC2 X3 결합부 clearance 복구
    - Y/H 돌출부 세로면을 3.6 mm inner margin으로 복구하고 가로 ledge relief만 유지
    - 6-Y X축 clearance 표시와 geometry verifier를 추가
    - DRC, Gerber/Drill, SpecKiwi evidence를 갱신
2026-06-05 chore: OPS-ARCH-002 KC2 X3 KiCad 산출물을 main 경로로 승격한다
    - X3 좌우 프로젝트를 hardware/kicad/kc2_left, hardware/kicad/kc2_right로 승격
    - soldered, hotswap, x1, x2 변형은 hardware/kicad/draft 아래에 보존
    - manifest, autoroute, file naming, fabrication ZIP, renders, verify scripts를 main 경로 기준으로 갱신
    - SRS evidence와 OPS-ARCH-002 verified 상태를 반영
2026-06-05 fix: KC2 X3 탭 축소로 nice!nano 안테나 keepout 충돌 해소
    배터리 carrier 패드와 불필요한 전원 넷을 제거해 컨트롤러 탭을 축소
    reset 스위치 위치와 후처리 라우팅을 조정해 nice!nano 안테나 keepout 및 M2 홀 간섭을 해소
    검증기, DRC, 렌더, Gerber, JLCPCB ZIP, docs/spec 증거를 갱신
2026-06-06 fix: KC2 X3 H4/H5 마운팅 홀 배치 조정
    H4를 한 줄 위로 옮기고 H2 인접 상단 코너에 H5를 추가해 하부 바닥판 고정 지점 분포를 개선
    왼쪽은 상단 외곽 제약 때문에 H2.x보다 안쪽인 x=173.45에 H5를 배치
    관련 산출물과 검증 증거를 동일 보드 상태로 재생성
2026-06-08 feat: KC2 X3 스크류리스 주문 패키지를 주문 가능 상태로 갱신한다
    스크류리스 레일 하우징용 주문 가능 상태를 확정하기 위해 M2 고정홀을 제거하고 REG_NPTH 등록홀, H1-H9 라벨, 배터리 리드 슬롯, antenna-side reset 위치, KC2 v1.0 L/R 실크를 반영한다.
    DRC, 연결성, 실크 간섭, 키캡 간격, Gerber/drill/render/JLCPCB ZIP 검증기를 보강하고 주문 산출물을 재생성한다.
    SpecKiwi 요구사항 증거와 Freerouting 프로세스 안전 규칙을 함께 갱신한다.
2026-06-10 CON-ARCH-003 하우징 걸쇠 검토 기록 추가
2026-06-15 CON-ARCH-003 하우징 산출물 추가
2026-06-23 Choc V2와 MX 하이브리드 요구사항 추가
